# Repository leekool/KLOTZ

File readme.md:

# KLOTZ EVQWGD001 MOD

**note: This is a modified version of the original KLOTZ PCB that replaces the EC12 rotary encoder with a EVQWD001 'roller wheel' encoder. In its current state the encoder is not reversible and only works on the right side, and there is also no push button support.

huge thank you to [Sadek Baroudi](https://github.com/sadekbaroudi)

TODO: 
- mirror EVQWD001 footprint for use on left side
- add push button support

<picture>
  <source media="(prefers-color-scheme: dark)" srcset="/docs/images/KLOTZ_font_dark.svg">
  <source media="(prefers-color-scheme: light)" srcset="/docs/images/KLOTZ_font_bright.svg">
  
</picture>

# KLOTZ SPLIT KEYBOARD

KLOTZ is a 34 key column-staggered choc split keyboard running [ZMK](https://zmk.dev/). It supports a low profile encoder, three status LEDs on every side and the SplitKB tenting puck.

## LAYOUT

## PCB

[Here](/PCB/) you can find the KiCad files and Gerbers for the KLOTZ.

## SWITCHPLATE

And [here](/switchplate/) is the switchplate, which you should use, if you plan to use hotswap sockets.

## KNOB

You can use pretty much any knob, which works with EC12 encoder, but [here](/knob/) you can find one, I designed for the KLOTZ.

## BUILD GUIDE

The build guide for the KLOTZ can be found [here](/docs/buildguide.md).

## FIRMWARE

[ZMK config](https://github.com/GEIGEIGEIST/zmk-config-klotz) for the KLOTZ.

## TRAVELCASE

Since a lot of people use the Amazon basics harddrive case (ZH1510147) for the KLOTZ I thought I should put an (affiliate) link in here. 

[US Amazon link](https://www.amazon.com/gp/product/B00F5CKWBA?ie=UTF8&psc=1&linkCode=ll1&tag=ekelhaigitspo-21&linkId=67f8dc497a4f2d7a740d78649fa4cf6d&language=us_EN&ref_=as_li_ss_tl)

[German Amazon link](https://www.amazon.de/gp/product/B00F5CKWBA?ie=UTF8&psc=1&linkCode=ll1&tag=ekelhaigitspo-21&linkId=67f8dc497a4f2d7a740d78649fa4cf6d&language=de_DE&ref_=as_li_ss_tl)

 If you build a KLOTZ I would be pretty happy to see some pictures. And if you want to leave me a tip you can do this [here](https://ko-fi.com/geigeigeist) (but please don't feel pressured)

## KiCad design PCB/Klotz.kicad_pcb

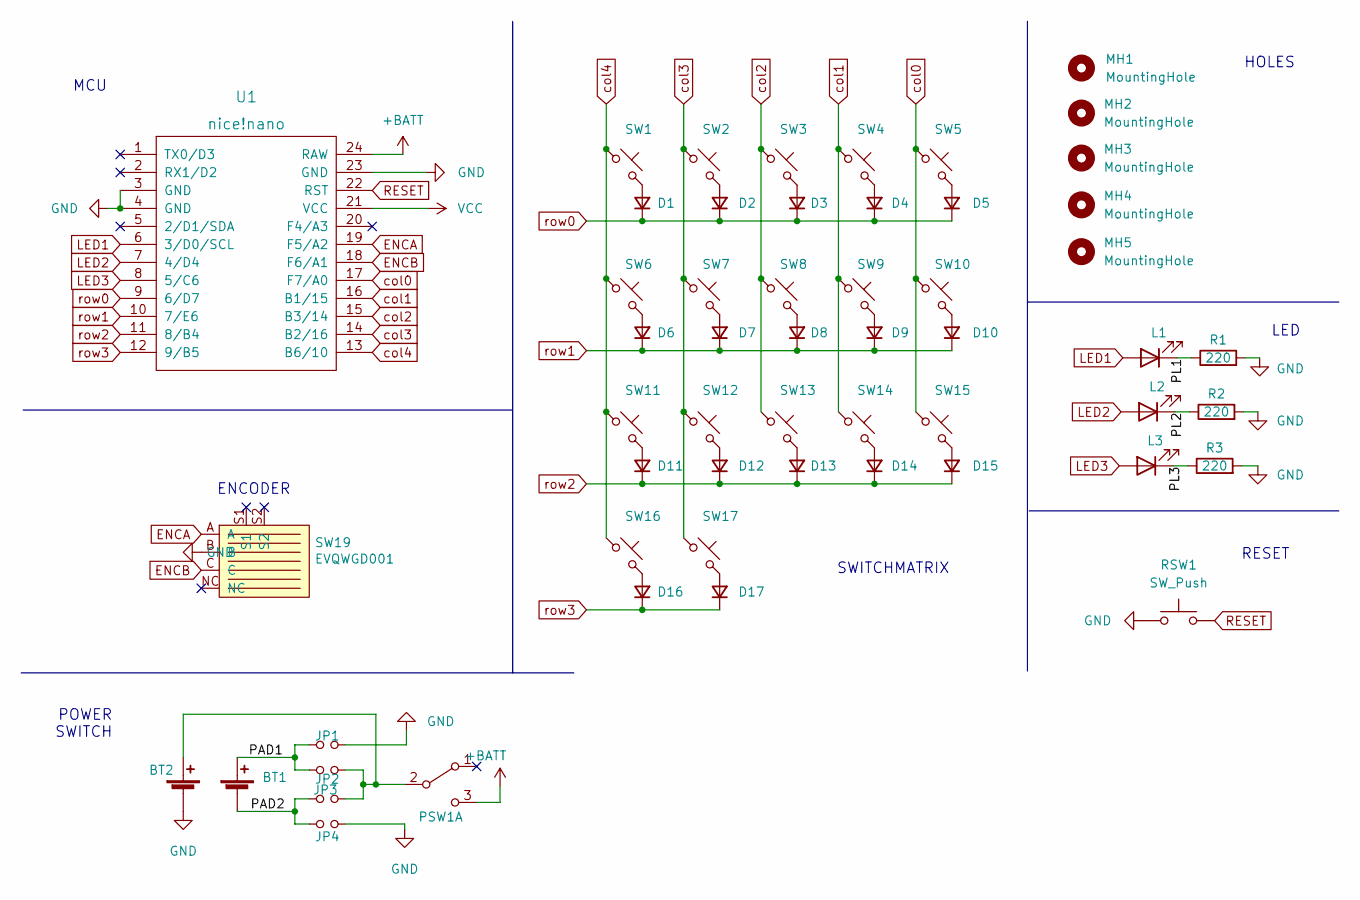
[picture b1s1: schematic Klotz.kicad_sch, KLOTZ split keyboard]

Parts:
BT1: Battery_Cell; JST_PH_reversible
BT2: Battery_Cell; custombatteryconnector
D1, D2, D3, D4, D5, D6, D7, D8, D9, D10, D11, D12, D13, D14, D15, D16, D17: D_Small; Diode_SOD123
JP1, JP2, JP3, JP4: Device_Jumper_NO_Small; Jumper
L1, L2, L3: LED; LED_3mm_reversible
MH1, MH2, MH3, MH4, MH5: MountingHole; MountingHole_2.2mm_M2_ISO7380_Pad
PSW1: SW_DPDT_x2; MSK12C02_reversible
R1, R2, R3: 220; R_1206_DoubleSided
RSW1: SW_Push; ResetSW
SW1, SW2, SW3, SW4, SW5, SW6, SW7, SW8, SW9, SW10, SW11, SW12, SW13, SW14, SW15, SW16, SW17: MX_SW_HS; Kailh_socket_PG1350_optional_reversible
SW19: EVQWGD001
U1: nice!nano; ProMicro_v2

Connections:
+BATT: PSW1.3 (C), U1.24 (RAW)
/PAD1: BT1.1 (+), JP1.1, JP2.1
/PAD2: BT1.2 (-), JP3.1, JP4.1
/PL1: L1.1 (K), R1.1
/PL2: L2.1 (K), R2.1
/PL3: L3.1 (K), R3.1
ENCA: SW19.A, U1.19 (F5/A2)
ENCB: SW19.C, U1.18 (F6/A1)
GND: BT2.2 (-), JP1.2, JP4.2, R1.2, R2.2, R3.2, RSW1.1, SW19.B, U1.3 (GND), U1.4 (GND), U1.23 (GND)
LED1: L1.2 (A), U1.6 (3/D0/SCL)
LED2: L2.2 (A), U1.7 (4/D4)
LED3: L3.2 (A), U1.8 (5/C6)
unnamed: BT2.1 (+), JP2.2, JP3.2, PSW1.2 (B)
unnamed: D1.2 (A), SW1.2
unnamed: D2.2 (A), SW2.2
unnamed: D3.2 (A), SW3.2
unnamed: D4.2 (A), SW4.2
unnamed: D5.2 (A), SW5.2
unnamed: D6.2 (A), SW6.2
unnamed: D7.2 (A), SW7.2
unnamed: D8.2 (A), SW8.2
unnamed: D9.2 (A), SW9.2
unnamed: D10.2 (A), SW10.2
unnamed: D11.2 (A), SW11.2
unnamed: D12.2 (A), SW12.2
unnamed: D13.2 (A), SW13.2
unnamed: D14.2 (A), SW14.2
unnamed: D15.2 (A), SW15.2
unnamed: D16.2 (A), SW16.2
unnamed: D17.2 (A), SW17.2
RESET: RSW1.2, U1.22 (RST)
VCC: U1.21 (VCC)
col0: SW5.1, SW10.1, SW15.1, U1.17 (F7/A0)
col1: SW4.1, SW9.1, SW14.1, U1.16 (B1/15)
col2: SW3.1, SW8.1, SW13.1, U1.15 (B3/14)
col3: SW2.1, SW7.1, SW12.1, SW17.1, U1.14 (B2/16)
col4: SW1.1, SW6.1, SW11.1, SW16.1, U1.13 (B6/10)
row0: D1.1 (K), D2.1 (K), D3.1 (K), D4.1 (K), D5.1 (K), U1.9 (6/D7)
row1: D6.1 (K), D7.1 (K), D8.1 (K), D9.1 (K), D10.1 (K), U1.10 (7/E6)
row2: D11.1 (K), D12.1 (K), D13.1 (K), D14.1 (K), D15.1 (K), U1.11 (8/B4)
row3: D16.1 (K), D17.1 (K), U1.12 (9/B5)

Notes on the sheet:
SWITCHMATRIX
POWER SWITCH
HOLES
LED
MCU
RESET
ENCODER

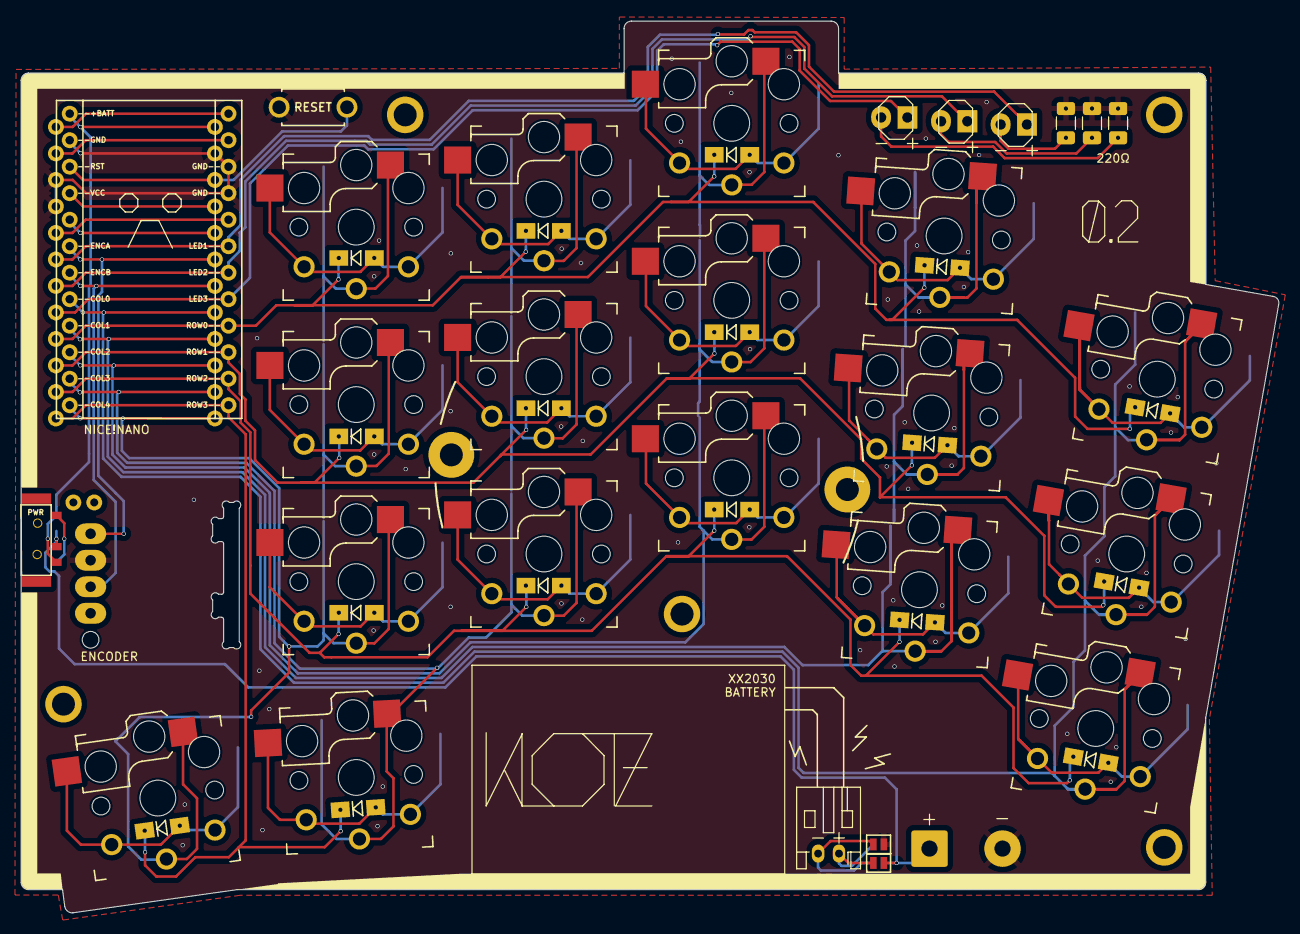
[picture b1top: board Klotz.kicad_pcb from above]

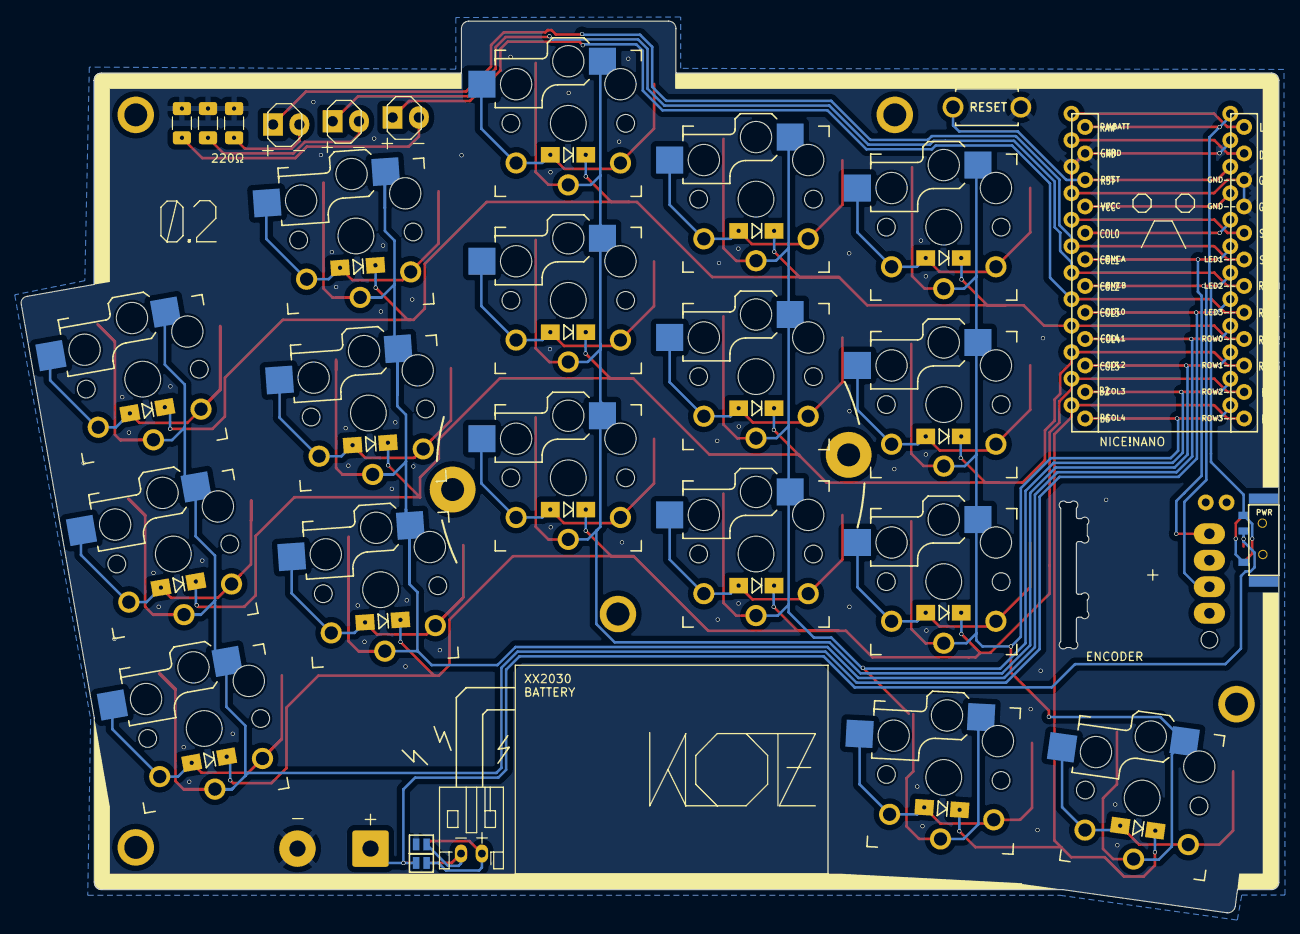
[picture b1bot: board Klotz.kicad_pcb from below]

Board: 2 copper layers, 120.5 x 85.5 mm, 55 parts (3 on the bottom side), 40 nets.

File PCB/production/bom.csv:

Designator,Footprint,Quantity,Value,LCSC Part #
BT1,JST_PH_reversible,1,Battery_Cell,
BT2,custombatteryconnector,1,Battery_Cell,
"D1, D10, D11, D12, D13, D14, D15, D16, D17, D2, D3, D4, D5, D6, D7, D8, D9",Diode_SOD123,17,D_Small,
"JP1, JP2, JP3, JP4",Jumper,4,Device_Jumper_NO_Small,
"L1, L2, L3",LED_3mm_reversible,3,LED,
"MH1, MH2, MH3, MH4, MH5",MountingHole_2.2mm_M2_ISO7380_Pad,5,MountingHole,
PSW1,MSK12C02_reversible,1,SW_DPDT_x2,
"R1, R2, R3",R_1206_DoubleSided,3,220,
RSW1,ResetSW,1,SW_Push,
"SW1, SW10, SW11, SW12, SW13, SW14, SW15, SW16, SW17, SW2, SW3, SW4, SW5, SW6, SW7, SW8, SW9",Kailh_socket_PG1350_optional_reversible,17,MX_SW_HS,
SW19,EVQWGD001,1,EVQWGD001,
U1,ProMicro_v2,1,nice!nano,

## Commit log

2023-06-07 init
2023-06-08 edit readme
2023-06-08 pcb gerbers
2023-06-08 switchplate gerbers
2023-06-08 gerber zips
2023-08-27 todo
